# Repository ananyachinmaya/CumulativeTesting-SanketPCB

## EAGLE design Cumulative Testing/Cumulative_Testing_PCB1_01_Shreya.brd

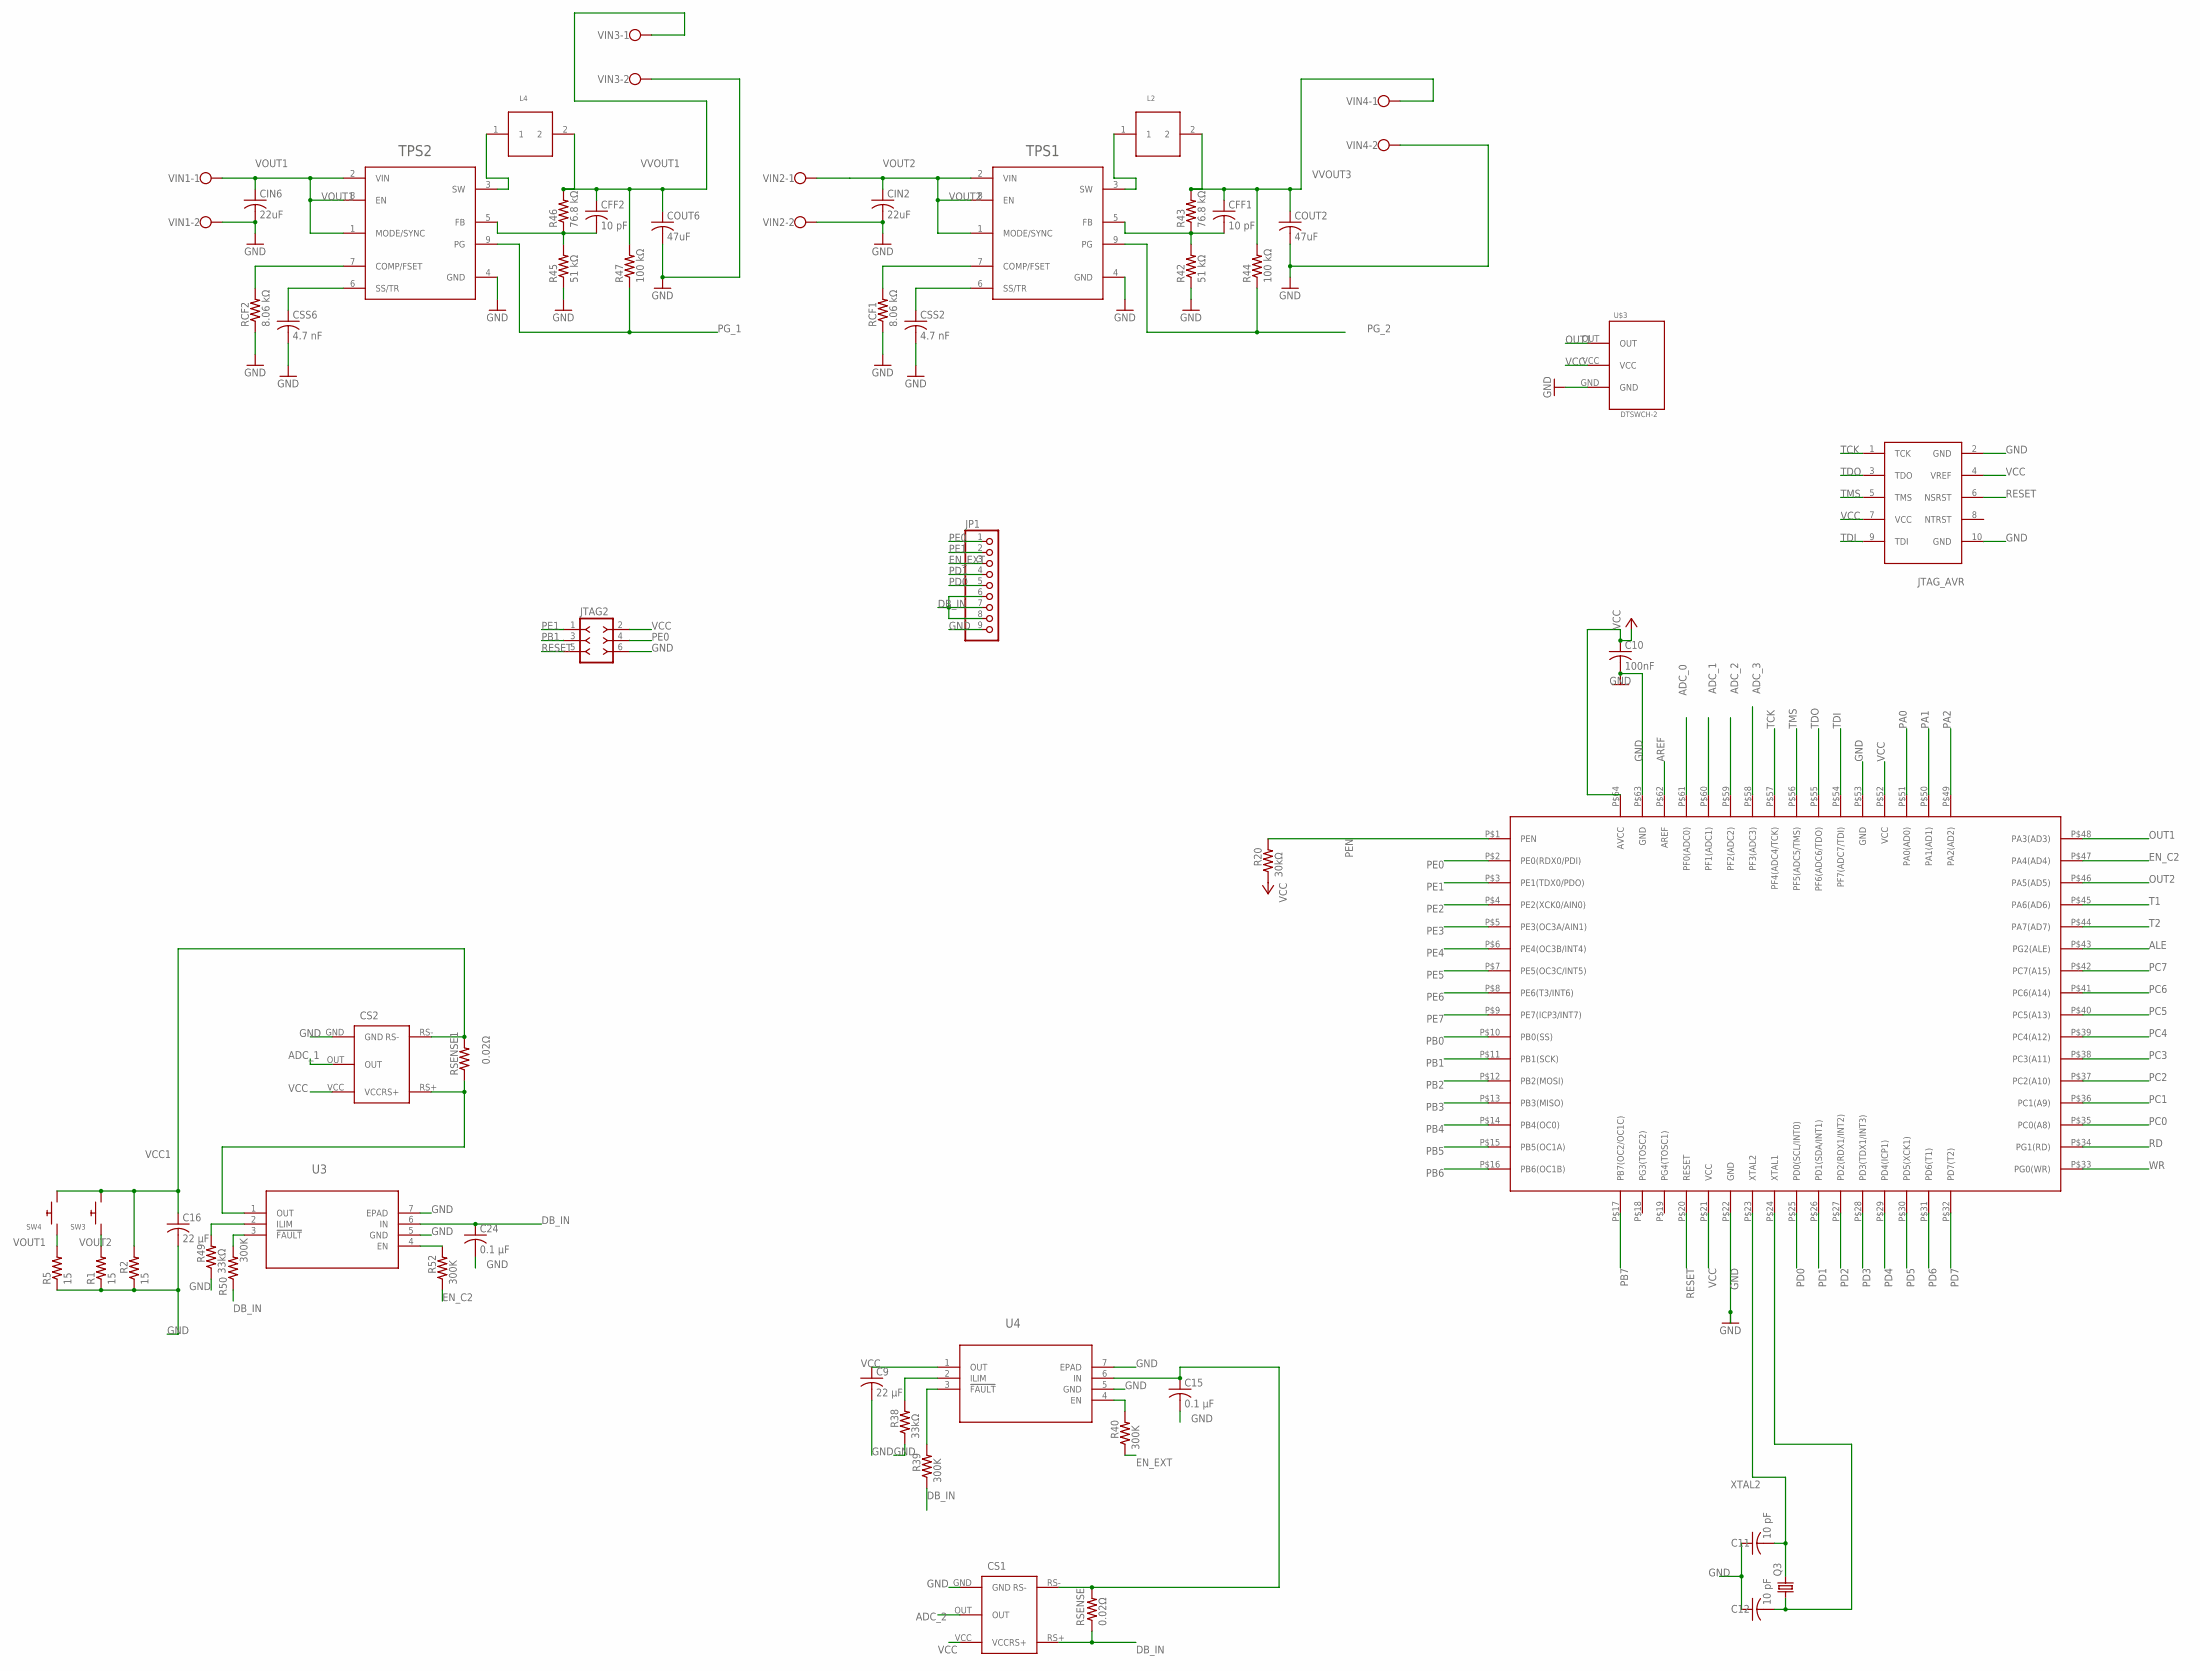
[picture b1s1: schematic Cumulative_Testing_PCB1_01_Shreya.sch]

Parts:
ATMEGA128: ATMEGAS128
C9, C16: 22 µF; C0805
C10: 100nF; C0805
C11, C12: 10 pF; C0805
C15, C24: 0.1 µF; C0805
CFF1, CFF2: 10 pF; C0805
CIN2, CIN6: 22uF; C0805
COUT2, COUT6: 47uF; C0805
CS1, CS2: MAX4372T
CSS2, CSS6: 4.7 nF; C0805
JP1: PINHD-1X9; 1X09-BIG
JTAG2: F-2X03-DIL-100; DIL-100-2X03
L2, L4: 0.56uH; XEL4020-561MEB
Q3: CRYSTALHC49U-V; HC49U-V
R1, R2, R5: 15; R0805
R20: 30kΩ; R0805
R38, R49: 33kΩ; R0805
R39, R40, R50, R52: 300K; R0805
R42, R45: 51 kΩ; R0805
R43, R46: 76.8 kΩ; R0805
R44, R47: 100 kΩ; R0805
RCF1, RCF2: 8.06 kΩ; R0805
RSENSE, RSENSE1: 0.02Ω; R0805
SW3, SW4: SWITCH_PUSHBUTTONC&K_KSS; BTN_CK_KSS
TPS1, TPS2: TPS62812
U3, U4: TPS25200DRVT_CURR_LIMIT; DRV6_1X1P6
U$1: JTAG_AVR
U$3: DTSWCH-2
VIN1, VIN2, VIN3, VIN4: W237-102

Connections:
ADC_0: ATMEGA128.P$61 (PF0(ADC0))
ADC_1: ATMEGA128.P$60 (PF1(ADC1)), CS2.OUT
ADC_2: ATMEGA128.P$59 (PF2(ADC2)), CS1.OUT
ADC_3: ATMEGA128.P$58 (PF3(ADC3))
ALE: ATMEGA128.P$43 (PG2(ALE))
AREF: ATMEGA128.P$62 (AREF)
DB_IN: C24.1, CS1.RS+, JP1.6, JP1.7, JP1.8, R39.1, R50.1, RSENSE.1, U3.6 (IN)
EN_C2: ATMEGA128.P$47 (PA4(AD4)), R52.1
EN_EXT: JP1.3, R40.1
GND: ATMEGA128.P$22 (GND), ATMEGA128.P$53 (GND), ATMEGA128.P$63 (GND), C9.2, C10.2, C11.1, C12.1, C15.2, C16.2, C24.2, CIN2.2, CIN6.2, COUT2.2, COUT6.2, CS1.GND, CS2.GND, CSS2.2, CSS6.2, JP1.9, JTAG2.6, R1.1, R2.1, R5.1, R38.1, R42.1, R45.1, R49.1, RCF1.1, RCF2.1, TPS1.4 (GND), TPS2.4 (GND), U3.5 (GND), U3.7 (EPAD), U4.5 (GND), U4.7 (EPAD), U$1.2 (GND), U$1.10 (GND), U$3.GND, VIN1.2, VIN2.2, VIN3.2, VIN4.2
unnamed: C15.1, CS1.RS-, RSENSE.2, U4.6 (IN)
unnamed: CS2.RS+, RSENSE1.1, U3.1 (OUT)
unnamed: ATMEGA128.P$24 (XTAL1), C12.2, Q3.1
unnamed: CFF1.2, R42.2, R43.1, TPS1.5 (FB)
unnamed: L2.1, TPS1.3 (SW)
unnamed: RCF1.2, TPS1.7 (COMP/FSET)
unnamed: CSS2.1, TPS1.6 (SS/TR)
unnamed: CFF2.2, R45.2, R46.1, TPS2.5 (FB)
unnamed: L4.1, TPS2.3 (SW)
unnamed: RCF2.2, TPS2.7 (COMP/FSET)
unnamed: CSS6.1, TPS2.6 (SS/TR)
unnamed: R49.2, U3.2 (ILIM)
unnamed: R50.2, U3.3 (!FAULT)
unnamed: R52.2, U3.4 (EN)
unnamed: R38.2, U4.2 (ILIM)
unnamed: R40.2, U4.4 (EN)
unnamed: R39.2, U4.3 (!FAULT)
OUT1: ATMEGA128.P$48 (PA3(AD3)), U$3.OUT
OUT2: ATMEGA128.P$46 (PA5(AD5))
PA0: ATMEGA128.P$51 (PA0(AD0))
PA1: ATMEGA128.P$50 (PA1(AD1))
PA2: ATMEGA128.P$49 (PA2(AD2))
PB0: ATMEGA128.P$10 (PB0(SS))
PB1: ATMEGA128.P$11 (PB1(SCK)), JTAG2.3
PB2: ATMEGA128.P$12 (PB2(MOSI))
PB3: ATMEGA128.P$13 (PB3(MISO))
PB4: ATMEGA128.P$14 (PB4(OC0))
PB5: ATMEGA128.P$15 (PB5(OC1A))
PB6: ATMEGA128.P$16 (PB6(OC1B))
PB7: ATMEGA128.P$17 (PB7(OC2/OC1C))
PC0: ATMEGA128.P$35 (PC0(A8))
PC1: ATMEGA128.P$36 (PC1(A9))
PC2: ATMEGA128.P$37 (PC2(A10))
PC3: ATMEGA128.P$38 (PC3(A11))
PC4: ATMEGA128.P$39 (PC4(A12))
PC5: ATMEGA128.P$40 (PC5(A13))
PC6: ATMEGA128.P$41 (PC6(A14))
PC7: ATMEGA128.P$42 (PC7(A15))
PD0: ATMEGA128.P$25 (PD0(SCL/INT0)), JP1.5
PD1: ATMEGA128.P$26 (PD1(SDA/INT1)), JP1.4
PD2: ATMEGA128.P$27 (PD2(RDX1/INT2))
PD3: ATMEGA128.P$28 (PD3(TDX1/INT3))
PD4: ATMEGA128.P$29 (PD4(ICP1))
PD5: ATMEGA128.P$30 (PD5(XCK1))
PD6: ATMEGA128.P$31 (PD6(T1))
PD7: ATMEGA128.P$32 (PD7(T2))
PE0: ATMEGA128.P$2 (PE0(RDX0/PDI)), JP1.1, JTAG2.4
PE1: ATMEGA128.P$3 (PE1(TDX0/PDO)), JP1.2, JTAG2.1
PE2: ATMEGA128.P$4 (PE2(XCK0/AIN0))
PE3: ATMEGA128.P$5 (PE3(OC3A/AIN1))
PE4: ATMEGA128.P$6 (PE4(OC3B/INT4))
PE5: ATMEGA128.P$7 (PE5(OC3C/INT5))
PE6: ATMEGA128.P$8 (PE6(T3/INT6))
PE7: ATMEGA128.P$9 (PE7(ICP3/INT7))
PEN: ATMEGA128.P$1 (PEN), R20.2
PG_1: R47.1, TPS2.9 (PG)
PG_2: R44.1, TPS1.9 (PG)
RD: ATMEGA128.P$34 (PG1(RD))
RESET: ATMEGA128.P$20 (RESET), JTAG2.5, U$1.6 (NSRST)
T1: ATMEGA128.P$45 (PA6(AD6))
T2: ATMEGA128.P$44 (PA7(AD7))
TCK: ATMEGA128.P$57 (PF4(ADC4/TCK)), U$1.1 (TCK)
TDI: ATMEGA128.P$54 (PF7(ADC7/TDI)), U$1.9 (TDI)
TDO: ATMEGA128.P$55 (PF6(ADC6/TDO)), U$1.3 (TDO)
TMS: ATMEGA128.P$56 (PF5(ADC5/TMS)), U$1.5 (TMS)
VCC: ATMEGA128.P$21 (VCC), ATMEGA128.P$52 (VCC), ATMEGA128.P$64 (AVCC), C9.1, C10.1, CS1.VCC, CS2.VCC, JTAG2.2, R20.1, U4.1 (OUT), U$1.4 (VREF), U$1.7 (VCC), U$3.VCC
VCC1: C16.1, CS2.RS-, R2.2, RSENSE1.2, SW3.P$2, SW4.P$2
VOUT1: CIN6.1, R5.2, SW4.P$1, TPS2.1 (MODE/SYNC), TPS2.2 (VIN), TPS2.8 (EN), VIN1.1
VOUT2: CIN2.1, R1.2, SW3.P$1, TPS1.1 (MODE/SYNC), TPS1.2 (VIN), TPS1.8 (EN)
VOUT3: VIN2.1
VVOUT1: CFF2.1, COUT6.1, L4.2, R46.2, R47.2, VIN3.1
VVOUT3: CFF1.1, COUT2.1, L2.2, R43.2, R44.2, VIN4.1
WR: ATMEGA128.P$33 (PG0(WR))
XTAL2: ATMEGA128.P$23 (XTAL2), C11.2, Q3.2

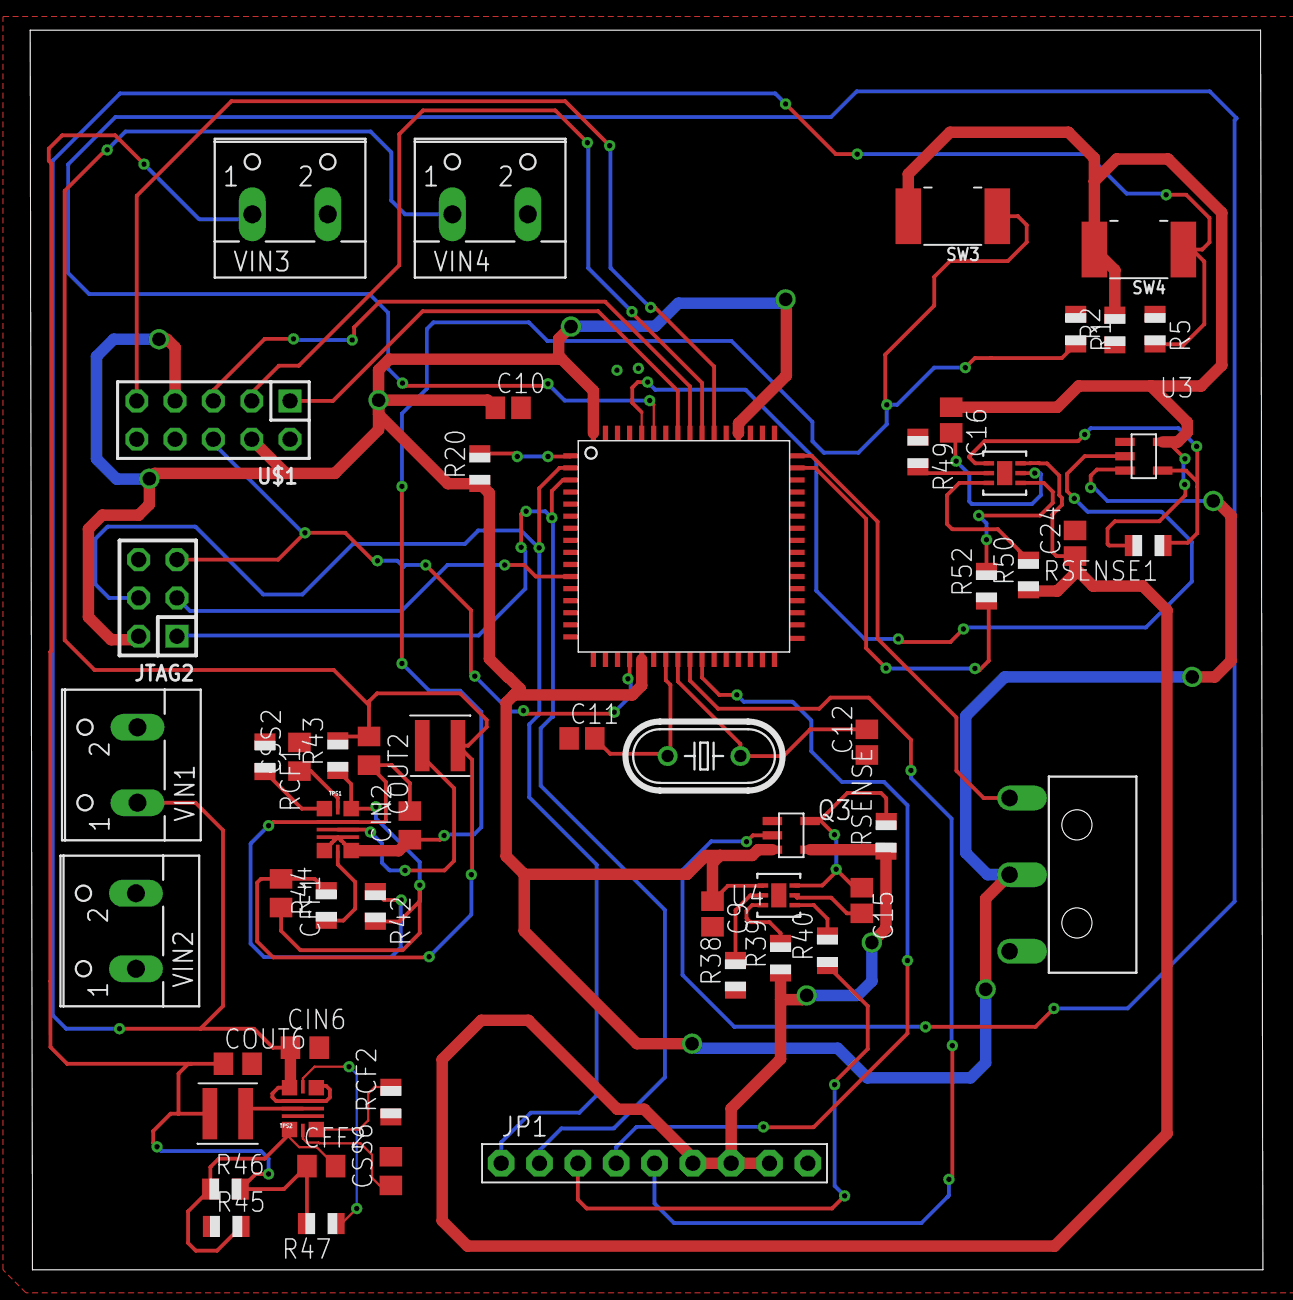
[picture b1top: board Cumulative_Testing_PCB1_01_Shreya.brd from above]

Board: 2 copper layers, 81.7 x 82.2 mm, 55 parts (0 on the bottom side), 44 nets.

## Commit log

2023-01-09 Added original PCB Schematic Files

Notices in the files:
parts and their libraries:
con-headers-jp: Copyright (C) 2008, Bob Starr
